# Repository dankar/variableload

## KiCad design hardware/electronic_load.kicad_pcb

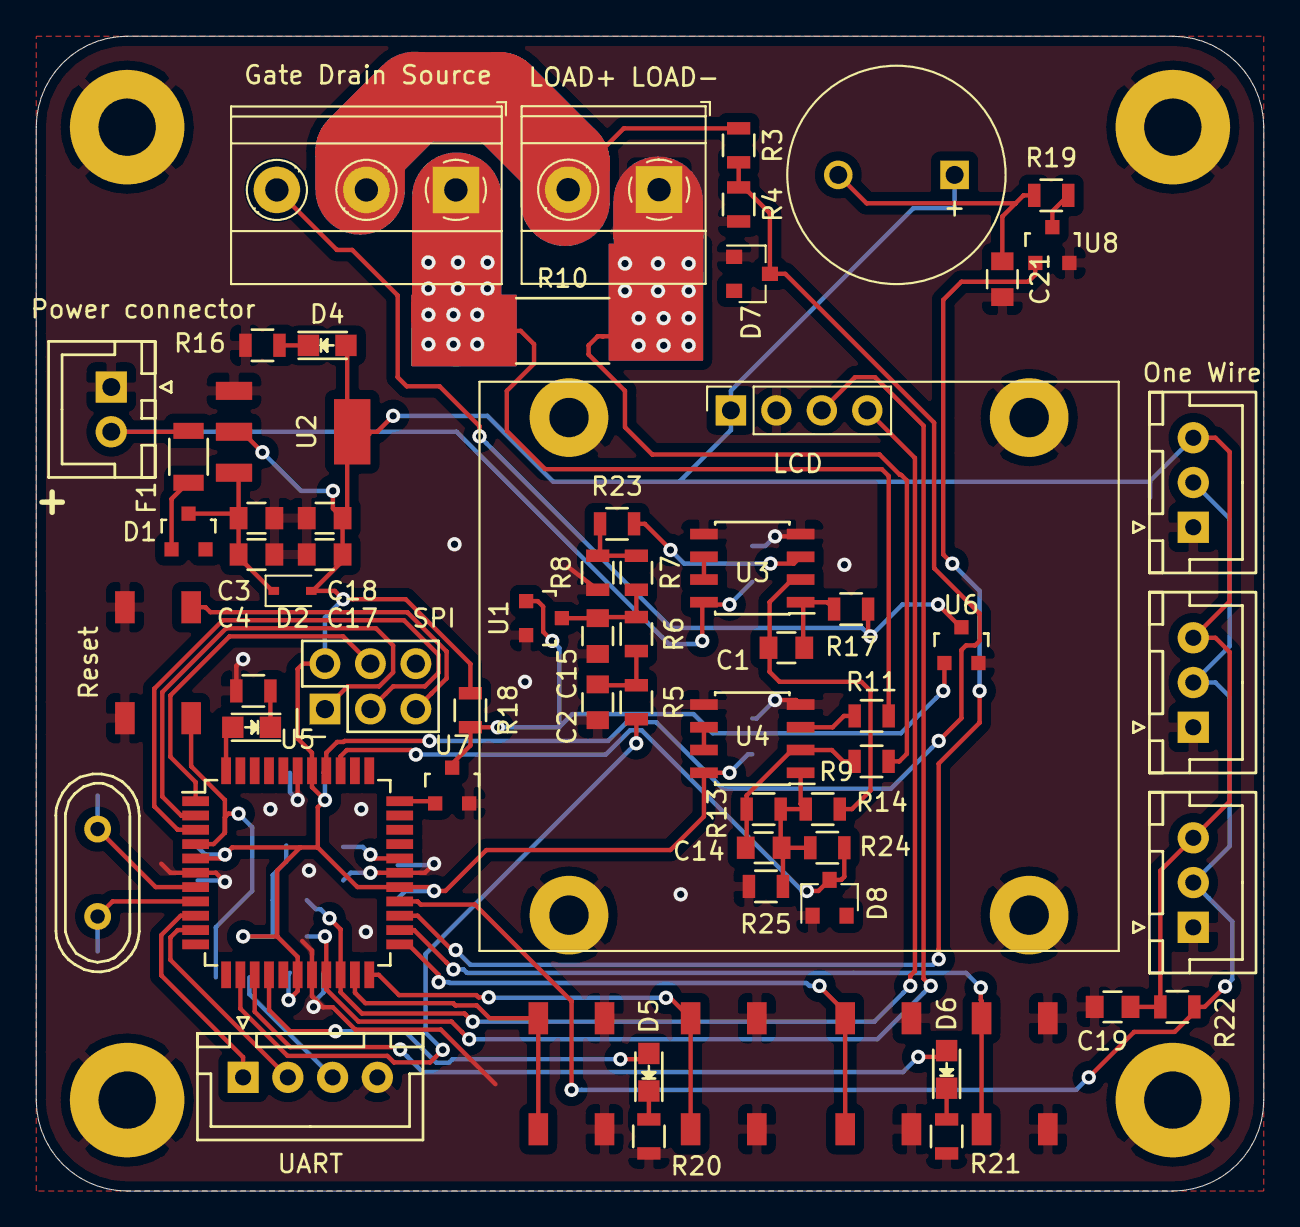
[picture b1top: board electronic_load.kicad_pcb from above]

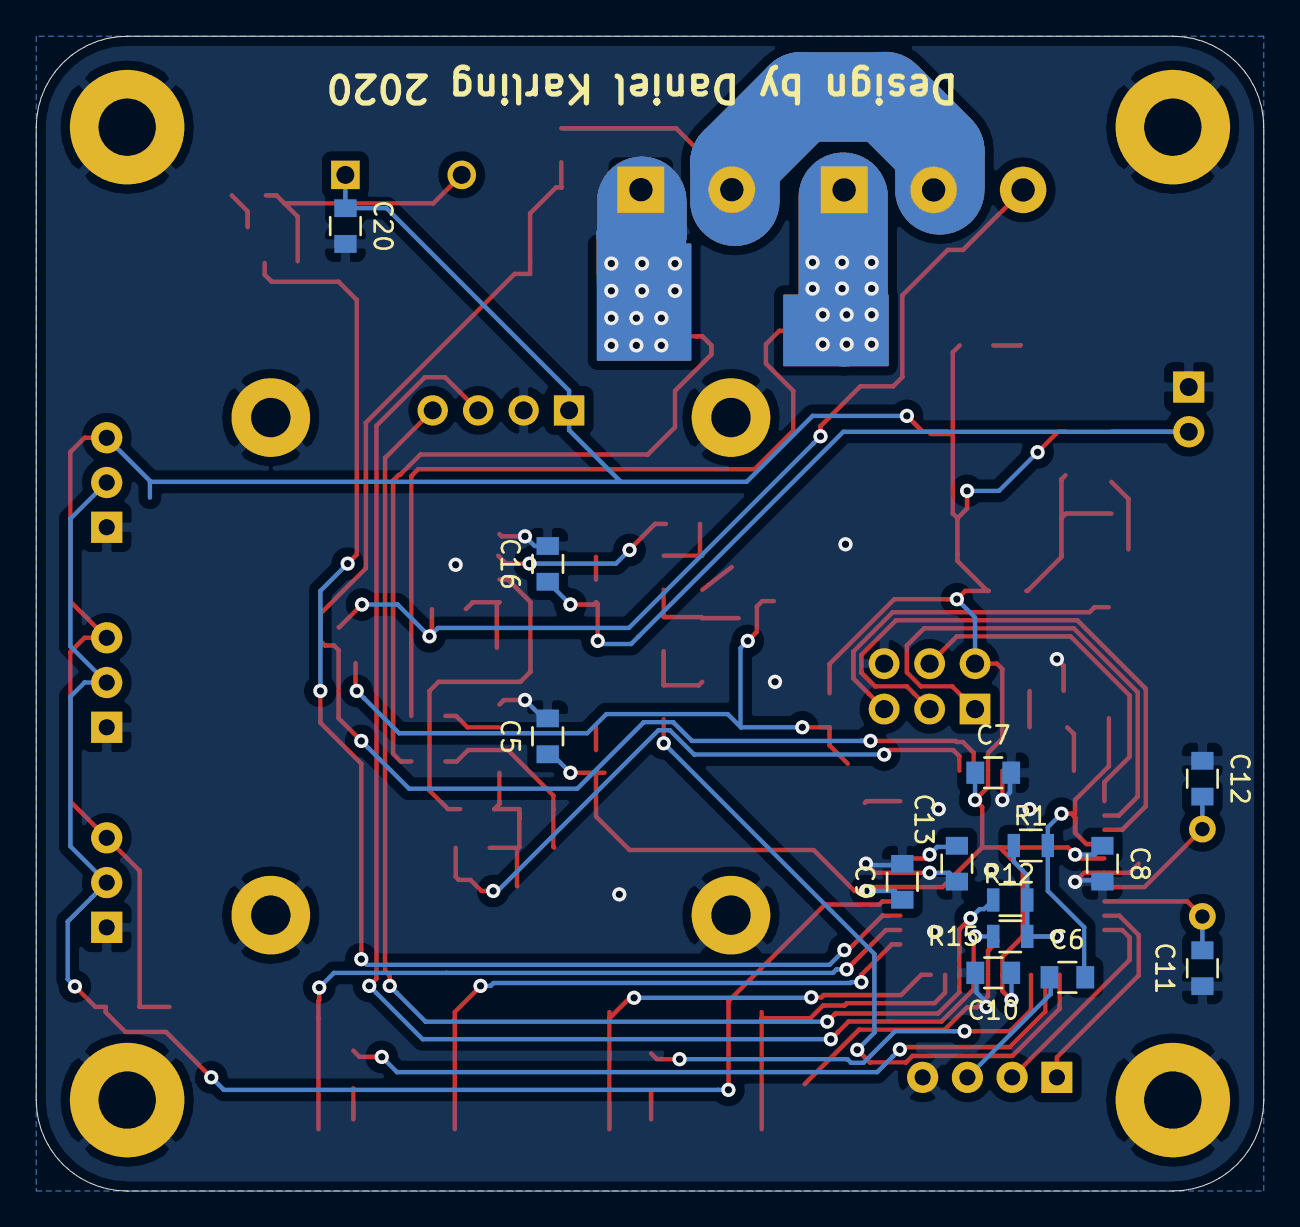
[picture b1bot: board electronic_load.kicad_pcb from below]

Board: 2 copper layers, 68.6 x 64.5 mm, 87 parts (14 on the bottom side), 51 nets.

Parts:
C1, C3, C17: 1u; C_0805
C2, C15: 470n; C_0805
C4, C5, C6, C7, C8, C9, C10, C13, C16, C18, C19, C20, C21: 100n; C_0805
C11, C12: 22p; C_0805
C14: 200n; C_0805
D1: BAT54C; SOT-23
D2: 1n4148; D_SOD-323
D3: Status 1; LED_0805
D4: LED; LED_0805
D5: Status 2; LED_0805
D6: Status 3; LED_0805
D7, D8: BZX84Cxx; D_SOT-23_ANK
F1: 0.25A; R_1206
H1, H2, H3, H4: LCD Mount; MountingHole_2.2mm_M2_Pad
H5, H6, H7, H8: PCB Mount; MountingHole_3.2mm_M3_Pad
J1: Screw_Terminal_01x02; TerminalBlock_Phoenix_MKDS-1,5-2-5.08_1x02_P5.08mm_Horizont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
J2: SPI; Pin_Header_Straight_2x03
J3: UART; JST_XH_B04B-XH-A_04x2.50mm_Straight
LS1: Speaker; MagneticBuzzer_ProSignal_ABT-410-RC
P1: Power connector; JST_XH_B02B-XH-A_02x2.50mm_Straight
P2: LCD; PinSocket_1x04_P2.54mm_Vertical
P3, P5, P6: One Wire; JST_XH_B03B-XH-A_03x2.50mm_Straight
P4: Gate Drain Source; TerminalBlock_Phoenix_MKDS-1,5-3_1x03_P5.00mm_Horizontal
R1, R18, R24, R25: 10k; R_0805
R2, R20, R21: 200; R_0805
R3, R13: 22k; R_0805
R4: 2k; R_0805
R5, R6: 100k; R_0805
R7: 120k; R_0805
R8: 1M; R_0805
R9, R17: 100; R_0805
R10: SHUNT, 0.01R; R_2512
R11, R14, R23: 1k; R_0805
R12, R15, R22: 4.7k; R_0805
R16: 200R; R_0805
R19: 120R; R_0805
SW1: Reset; Switch
SW2: Back; Switch
SW3: Down; Switch
SW4: Up; Switch
SW5: Enter; Switch
U1, U6, U7, U8: FDV303N; SOT-23
U2: TLV1117-33; SOT-223
U3: LM358; SOIC-8_3.9x4.9mm_Pitch1.27mm
U4: MCP6002-xSN; SOIC-8_3.9x4.9mm_Pitch1.27mm
U5: ATmega1284P-AU; TQFP-44_10x10mm_Pitch0.8mm
Y1: 16MHz; Crystal_HC49-U_Vertical

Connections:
3.3V: C5.1, C7.1, C8.1, C9.1, C10.1, C17.1, C18.1, C19.1, C20.1, D2.2, D4.2, J2.2, LS1.1, P2.1, P3.3, P5.3, P6.3, R1.2, R12.2, R15.2, R18.1, R22.2, U2.2, U4.8, U5.5, U5.17, U5.27, U5.38
12V: C16.1, F1.2, P1.2, U3.8
/MCU/AREF: C13.1, U5.29
/MCU/BUTTON1: SW5.2, U5.24
/MCU/BUTTON2: SW4.2, U5.23
/MCU/BUTTON3: SW3.2, U5.22
/MCU/BUTTON4: SW2.2, U5.21
/MCU/DTR: C6.1, J3.3
/MCU/MISO: J2.1, U5.2
/MCU/MOSI: J2.4, U5.1
/MCU/RESET: C6.2, J2.5, R1.1, SW1.1, U5.4
/MCU/SCK: J2.3, U5.3
/MCU/UART_RX: J3.1, U5.9
/MCU/UART_TX: J3.2, U5.10
/Power Supply/V12_fused: C3.1, C4.1, D1.3, D2.1, U2.3
/Variable Load/Current_feedback_P: P4.1, R10.1, R11.1
/Variable Load/Enable_inv: R18.2, U1.1, U6.1, U7.3
/Variable Load/Gate_drive: C1.1, R17.2, U3.1
/Variable Load/Iset_filtered: C15.1, R6.1, R7.1, U1.3
/Variable Load/Vload: J1.2, P4.2, R3.1
CURRENT_SENSE: C14.2, R9.2, R13.2, R24.1, R25.1, U4.1
Enable: U5.33, U7.1
GND: C2.2, C3.2, C4.2, C5.2, C7.2, C8.2, C9.2, C10.2, C11.1, C12.1, C13.2, C15.2, C16.2, C17.2, C18.2, C19.2, C20.2, C21.2, D7.2, D8.2, H1.1, H2.1, H3.1, H4.1, H5.1, H6.1, H7.1, H8.1, J1.1, J2.6, J3.4, P1.1, P2.2, P3.1, P5.1, P6.1, R2.2, R4.2, R8.2, R10.2, R16.2, R20.2, R21.2, R25.2, SW1.2, SW2.1, SW3.1, SW4.1, SW5.1, U1.2, U2.1, U3.4, U3.5, U4.4, U4.5, U5.6, U5.18, U5.28, U5.39, U6.2, U7.2, U8.2
Iset: R5.2, U5.13
unnamed: C1.2, R9.1, U3.2
unnamed: C2.1, R5.1, R6.2
unnamed: C11.2, U5.8, Y1.2
unnamed: C12.2, U5.7, Y1.1
unnamed: C14.1, R13.1, R14.1, U4.2
unnamed: C21.1, LS1.2, R19.1
unnamed: D1.1, F1.1
unnamed: D3.1, R2.1
unnamed: D4.1, R16.1
unnamed: D5.1, R20.1
unnamed: D6.1, R21.1
unnamed: D8.1, R24.2, U5.36
unnamed: P4.3, R17.1, U6.3
unnamed: R11.2, U4.3
unnamed: R19.2, U8.3
unnamed: R7.2, R8.1, R23.1
unnamed: R23.2, U3.3
unnamed: U3.6, U3.7
unnamed: U4.6, U4.7
ONE_WIRE: P3.2, P5.2, P6.2, R22.1, U5.26
SCL: P2.3, R15.1, U5.19
SDA: P2.4, R12.1, U5.20
SPEAKER_DRIVE: U5.25, U8.1
STATUS_1: D3.2, U5.44
STATUS_2: D5.2, U5.15
STATUS_3: D6.2, U5.14
VOLTAGE_SENSE: D7.1, R3.2, R4.1, U5.37

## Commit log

2020-04-20 Blebleble
2020-04-20 Fixup
2020-04-22 Fixes
2020-08-11 First commit of code
